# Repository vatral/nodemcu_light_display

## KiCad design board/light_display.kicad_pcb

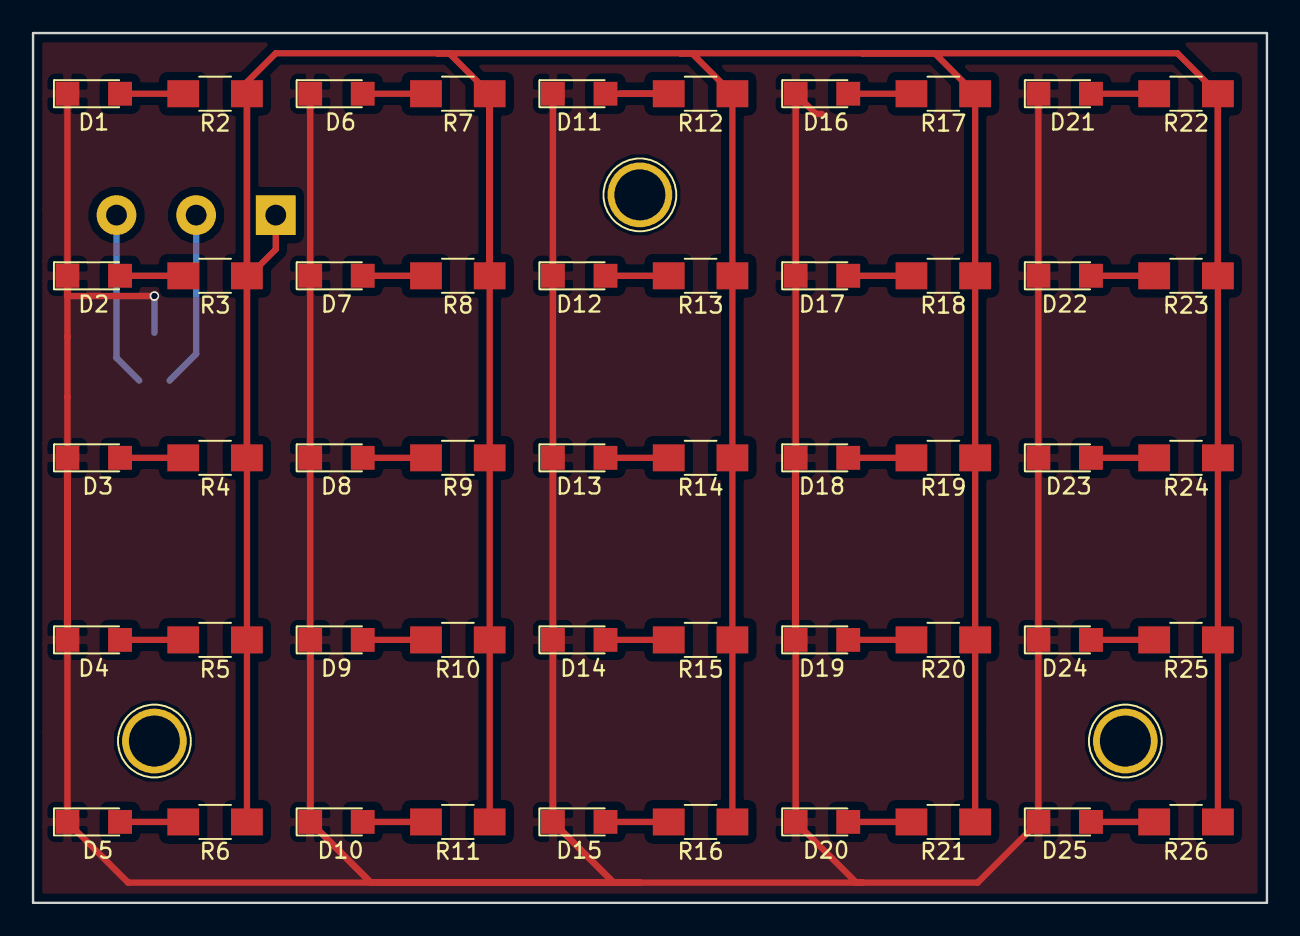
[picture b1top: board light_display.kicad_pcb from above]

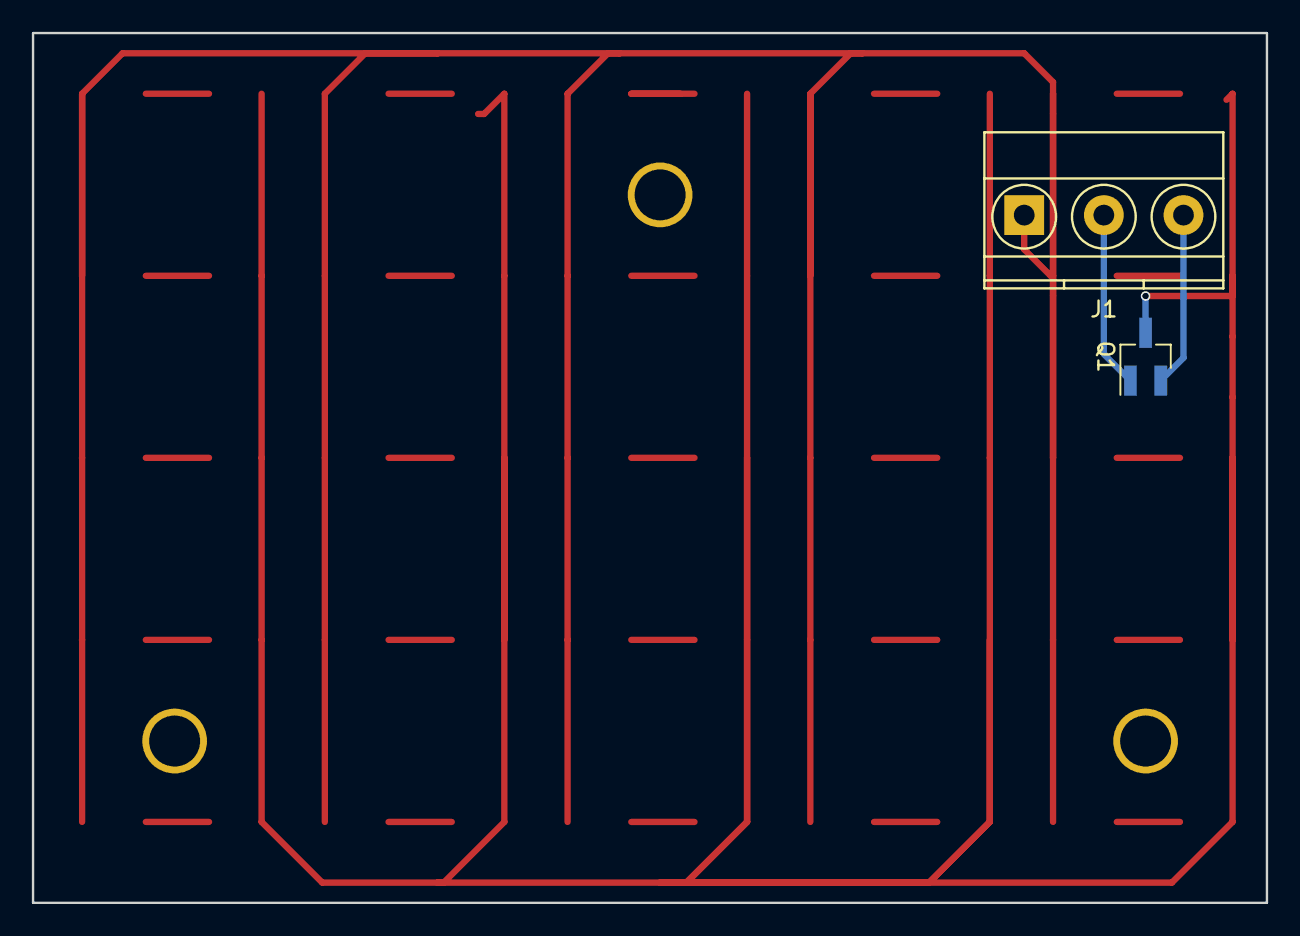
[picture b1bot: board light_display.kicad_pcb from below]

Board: 2 copper layers, 77.5 x 54.6 mm, 52 parts (2 on the bottom side), 29 nets.

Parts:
D1, D2, D3, D4, D5, D6, D7, D8, D9, D10, D11, D12, D13, D14, D15, D16, D17, D18, D19, D20, D21, D22, D23, D24, D25: LED; LED_1206
J1: Screw_Terminal_1x03; TerminalBlock_Pheonix_MKDS1.5-3pol
Q1: Q_NPN_BEC; SOT-23_Handsoldering
R2, R3, R4, R5, R6, R7, R8, R9, R10, R11, R12, R13, R14, R15, R16, R17, R18, R19, R20, R21, R22, R23, R24, R25, R26: 90; R_1206_HandSoldering

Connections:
unnamed: D1.1, D2.1, D3.1, D4.1, D5.1, D6.1, D7.1, D8.1, D9.1, D10.1, D11.1, D12.1, D13.1, D14.1, D15.1, D16.1, D17.1, D18.1, D19.1, D20.1, D21.1, D22.1, D23.1, D24.1, D25.1, Q1.3
unnamed: D1.2, R2.2
unnamed: D2.2, R3.2
unnamed: D3.2, R4.2
unnamed: D4.2, R5.2
unnamed: D5.2, R6.2
unnamed: D6.2, R7.2
unnamed: D7.2, R8.2
unnamed: D8.2, R9.2
unnamed: D9.2, R10.2
unnamed: D10.2, R11.2
unnamed: D11.2, R12.2
unnamed: D12.2, R13.2
unnamed: D13.2, R14.2
unnamed: D14.2, R15.2
unnamed: D15.2, R16.2
unnamed: D16.2, R17.2
unnamed: D17.2, R18.2
unnamed: D18.2, R19.2
unnamed: D19.2, R20.2
unnamed: D20.2, R21.2
unnamed: D21.2, R22.2
unnamed: D22.2, R23.2
unnamed: D23.2, R24.2
unnamed: D24.2, R25.2
unnamed: D25.2, R26.2
unnamed: J1.1, R2.1, R3.1, R4.1, R5.1, R6.1, R7.1, R8.1, R9.1, R10.1, R11.1, R12.1, R13.1, R14.1, R15.1, R16.1, R17.1, R18.1, R19.1, R20.1, R21.1, R22.1, R23.1, R24.1, R25.1, R26.1
unnamed: J1.2, Q1.1
unnamed: J1.3, Q1.2

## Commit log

2018-09-19 Initial version
